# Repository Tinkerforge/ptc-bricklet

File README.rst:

PTC Bricklet
============

This repository contains the firmware source code and the hardware design
files. The documentation generator configs can be found at
https://github.com/Tinkerforge/generators

Repository Content
------------------

software/:
 * examples/: Examples for all supported languages
 * build/: Compiled files
 * src/: Source code of firmware
 * Makefile: Makefile to build project

hardware/:
 * Contains KiCad project files and additionally schematics as PDF

datasheets/:
 * Contains datasheets for sensors and complex ICs that are used

Hardware
--------

The hardware is designed with the open source EDA Suite KiCad
(http://www.kicad.org). Before you are able to open the files,
you have to install the Tinkerforge kicad-libraries
(https://github.com/Tinkerforge/kicad-libraries). You can either clone
them directly in hardware/ or clone them in a separate folder and
symlink them into hardware/
(ln -s kicad_path/kicad-libraries project_path/hardware). After that you
can open the .pro file in hardware/ with KiCad and from there view and
modify the schematics and the PCB layout.

Software
--------

If you want to do your own Brick/Bricklet firmware development we highly
recommend that you use our build environment setup script and read the
tutorial (https://www.tinkerforge.com/en/doc/Tutorials/Tutorial_Build_Environment/Tutorial.html).

To compile the C code we recommend you to install the newest GNU Arm Embedded
Toolchain (https://launchpad.net/gcc-arm-embedded/+download).
You also need to install bricklib (https://github.com/Tinkerforge/bricklib)
and brickletlib (https://github.com/Tinkerforge/brickletlib).

You can either clone it directly in software/src/ or clone it in a
separate folder and symlink it into software/src/
(ln -s bricklib_path/bricklib project_path/software/src/ and
ln -s brickletlib_path/brickletlib project_path/software/src/).
Finally make sure to have CMake installed
(http://www.cmake.org/cmake/resources/software.html).

After that you can build the firmware by invoking make in software/.
The firmware (.bin) can then be found in software/build/ and uploaded
with brickv (click button "Flashing" on start screen).

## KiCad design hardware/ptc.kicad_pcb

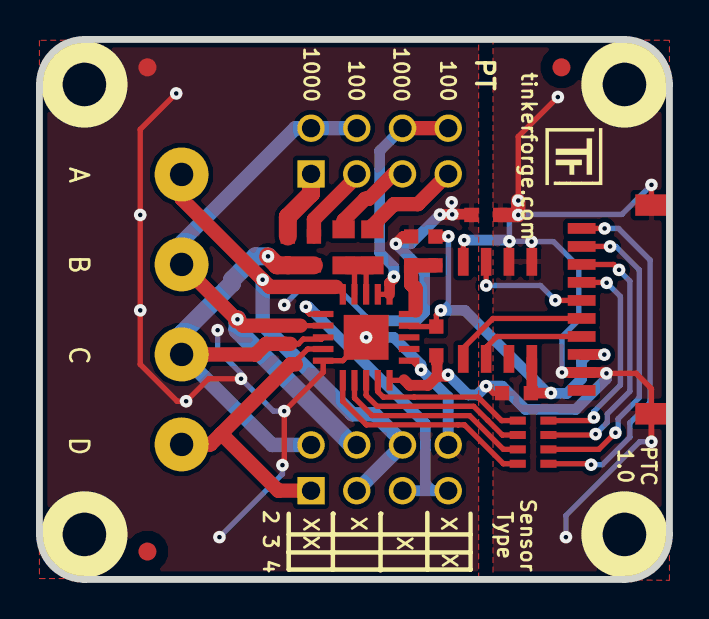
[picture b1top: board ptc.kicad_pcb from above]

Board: 2 copper layers, 35.0 x 30.0 mm, 26 parts (0 on the bottom side), 26 nets.

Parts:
C1, C2, C3, C5: 100nF; C0603
C4: 10nF; C0603
FB1, FB2: FB; C0603
Fiducial_Mark: VAL**; Fiducial_Mark
Fiducial_Mark#2, Fiducial_Mark#3: VAL**; Fiducial_Mark
J1, J2: AKL_5_2
P1: CON-SENSOR
P2, P3: CONN_02X04; pin_array_4x2
R1: 390 0.1%; R0805
R2: 3k9 0.1%; R0805
RP1: 100; 0603X4
U1: M24C64; SOIC8
U2: MAX31865; QFN-20-5x5
U3, U4, U5, U6: DRILL; DRILL_NP
VAL: CE_5mm
VAL#2: WEEE_7mm

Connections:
AGND: C3.2, FB1.2, P3.8, U2.10, U2.16, U2.EP
FORCE2: P3.5, P3.7, U2.6
FORCE+: J1.2, P3.3, P3.6, U2.5
FORCE-: J2.1, P3.1, U2.9
GND: C1.2, C2.1, FB1.1, P1.2, P1.EP, U1.1, U1.2, U1.4, U2.15
unnamed: C3.1, FB2.1, U2.20
unnamed: C4.2, P2.3
unnamed: C5.2, P2.1
unnamed: P1.4, U1.6
unnamed: P1.5, U1.5
unnamed: P1.6, U1.3
unnamed: P1.7, RP1.8
unnamed: P1.8, RP1.7
unnamed: P1.9, RP1.6
unnamed: P1.10, RP1.5
unnamed: P2.5, R2.1
unnamed: P2.6, P2.8, U2.1, U2.2
unnamed: P2.7, R1.1
unnamed: R1.2, R2.2, U2.3, U2.4
unnamed: RP1.1, U2.14
unnamed: RP1.2, U2.13
unnamed: RP1.3, U2.12
unnamed: RP1.4, U2.11
RTDIN+: J1.1, P2.2, P2.4, P3.4, U2.7
RTDIN-: C4.1, C5.1, J2.2, P3.2, U2.8
VCC: C1.1, C2.2, FB2.2, P1.3, U1.8, U2.19

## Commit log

2013-01-14 Fix name in readme
2013-04-12 Add missing API and moving average
2013-06-20 Add Examples for PTC Bricklet
2013-06-21 Simplify API for PTC wire mode
2013-06-25 Hardware Files Checkin
2013-07-03 Add debugging, fix defines for newest hardware version
2013-08-13 Add shell examples
2013-08-16 shell: Fix syntax error
2013-08-21 windows: Don't trigger a build in generate_makefile.bat
    Also use normal make instead of a special named one.
2013-12-19 Fix wrong length for GetDebounce packet (through brickletlib)
2014-01-10 Add Perl examples
2014-01-15 php: Use const for constant values
2014-02-07 Add Mathematica examples
2014-02-10 perl: fixed namespace
2014-02-12 javascript: add examples
2014-02-18 javascript: examples fixed
2014-02-20 javascript: add html examples
2014-02-24 javascript: port 4280, startExample()
2014-02-28 javascript: Break long lines and cleanup whitespace
2014-03-05 Add LabVIEW examples
2014-03-06 labview: Add examples in LV2010 format
2014-03-31 matlab: add examples
2014-04-02 java: Unify constants style
2014-04-02 perl: Unify print style
2014-04-17 matlab: Adapt examples to new callback style
2014-04-17 matlab: Add parentheses to make pygments happy
2014-07-15 java: Replace System.console() usage with an Eclipse compatible pattern
2014-12-02 Use ReadLine instead of ReadKey for C# example
2015-02-13 vbnet: Use ReadLine instead of ReadKey
    Because ReadKey doesn't work with a pipe as stdin on the RED Brick.
2015-03-02 windows: Stop cmake from searching for mingw32-make.exe
    Using MinGW Makefiles as generator makes cmake search for mingw32-make.exe
    which might not be installed because GnuWin32's make.exe is used instead.
2015-04-09 c: Whitespace
2015-06-24 javascript: Clean up output creation
2015-07-25 Make JavaScript browser example textarea readonly
2015-07-27 Cleanup C/C++, C#, Java, Python and Ruby examples
2015-07-29 Reformat changelog
2015-08-07 Use full device class name in Python examples
2015-08-12 Fix minor warnings in C/C++ examples
2015-08-14 Cleanup Delphi examples
2015-08-18 Cleanup VB.NET examples
2015-08-19 Cleanup Perl examples
2015-09-09 Duplicate cmake call to fix bug during cmake creation
2015-09-30 Generator based example cleanup
2015-11-12 matlab: Fix callback handling for R2014a
    http://undocumentedmatlab.com/blog/matlab-callbacks-for-java-events-in-r2014a
2015-11-25 Include date and commit into changelog
2016-05-18 c: Add missing device destroy call
2016-07-01 Make the change UID comment more explicit
2017-04-13 csharp: Adapt example
2017-04-21 shell: Adapt example
2017-06-02 octave: Use javaObject instead of deprecated java_new
2017-08-04 Add 3d information (final)
2017-08-04 Add 3d model (*.step & *.FCStd)
2017-08-16 fix library settings
2017-11-30 Update examples from generator
2017-12-07 mathematica: Also generate .nb files
2018-02-02 Update examples
2018-02-19 javascript: Close div tag correctly
2018-02-20 Cleanup KiCad libraries config
    Ensure LibDir=kicad-libraries and LibName1=tinkerforge.
    Remove special library.
2018-04-18 Add SensorConnectedCallback API implementation
2018-04-18 Update changelog
2018-05-24 perl: Use strict in examples
2018-07-11 Add Makefile with docker support
2018-07-11 Update directory structure and build instructions
2018-07-11 Remove obsolete generate_makefile scripts
2018-11-06 Add rust examples
2018-11-07 rust: Accept host names for ip connection, fix naming inconsistencies
2018-11-07 rust: Rename callback receivers.
2018-12-14 Add go examples.
2018-12-14 go: Fix printf parameters.
2018-12-18 go: Change import path.
2018-12-18 go: Change import path again.
2018-12-20 rust: Reformat examples.
2019-01-24 mqtt: Add examples.
2019-01-24 mqtt: Fix example header.
2019-01-24 mqtt: Remove executable bit in example permissions.
2019-01-24 go: Minor example fixes.
2019-01-24 mqtt: Minor example fixes.
2019-03-28 mqtt: Fix whitespace.
2019-08-22 c: Adapt to bindings changes
2020-01-13 examples: Use python3 input instead of python2 raw_input.
2020-01-13 examples: mqtt: Remove trailing whitespace.
2021-10-25 Update KiCad link
    https://www.kicad.org/blog/2021/10/Avoid-links-to-former-kicad-domain/
2022-07-06 Add license files.

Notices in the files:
hardware/ptc.kicad_pcb:
Licensed under CERN OHL v.1.1
Copyright (©) 2013, B.Nordmeyer
Copyright Tinkerforge GmbH 2013.
This documentation describes Open Hardware and is licensed under the
CERN OHL v. 1.1.
